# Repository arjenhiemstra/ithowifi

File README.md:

# ithowifi
ESP based WiFi controller for Itho devices

*(note: I'm in no way a professional hardware/software engineer and have no background in these subjects. I like this for a hobby, to learn and to share my projects)*

Finished boards can be ordered in my webshop:
[https://www.nrgwatch.nl](http://www.nrgwatch.nl)
or in my Tindie store:
[https://www.tindie.com/products/19680/](https://www.tindie.com/products/19680/)

|CVE Add-on|non-CVE wifi module|
|:---:|:---:|
|  |  |

## WiFi add-on to control itho central ventilation units

-   Control your Itho Daalderop ventilation unit with one simple add-on module
-   No hardware changes needed to the Itho unit, no warranty void
-   Control fan speed through the web interface, REST API v2, MQTT, or Home Assistant
-   Send remote commands via virtual remotes (I2C) or RF remotes (CC1101 wireless)
-   RF standalone mode for devices without I2C connection (e.g. HRU 400 R)
-   OTA firmware updates directly from the web interface
-   Easily integrate in any home automation system through MQTT or REST API
-   Companion integrations available:
    - [Home Assistant](https://github.com/arjenhiemstra/ithowifi-ha-integration) (REST API, automatic discovery)
    - [Home Assistant](https://github.com/jasperslits/haithowifi) (MQTT API, feature rich)
    - [Homey](https://homey.app/en-nl/app/nl.monkeysoft.nrgwatch/Itho-Daalderop/) (REST API)
-   Installation can be done in minutes
-   Detailed installation manual and setup wizard

### CVE models (IthiWiFi CVE add-on - I2C):
-   CVE ECO 2 (also sold by 'Heatrae Sadia' in the UK)
-   CVE ECO RFT (SE/SP, HE/HP)
-   CVE-S ECO / PAK / Optima / CO2
-   HRU ECO 150E / 150P
-   HRU ECO 200E / 200P (also sold as 'Elektrodesign EHR 140 Akor BP' and 'Heatrae Sadia Advance Plus')

### NON-CVE models (IthiWiFi NON-CVE add-on - I2C):
-   HRU ECO 350 LR / LP / HR / HP
-   HRU ECO LE / HE / LP / HP BAL
-   HRU 3 (3) and HRU 3 (2)
-   HRU ECO 250R / 250P, HRU ECO 300R / 300P and HRU ECO 300 DUO Zone (with adapter board, PCI-e splitter cable and CC1101)
-   DemandFlow / QualityFlow
-   WPU 4G / 5G (heat pump)
-   AutoTemp

### RF standalone mode (IthiWiFi NON-CVE add-on wuth CC1101):
-   HRU 300V, HRU 375V and HRU 400 R
-   Most Itho devices controllable via RF (CC1101 module required)
-   Status data received wirelessly via 31DA/31D9 RF messages
-   Older Itho units that only know the RF protocol from before RAMSES (tested on a CVE ECO 2): send only, with a remote of type "RF (old protocol)"

### HRU models by article number:
Check the article number on the nameplate/sticker of your Itho. x is any digit. A letter after the number (A, S) does not count.

| Model | Article number | Add-on |
|---|---|---|
| HRU ECO 150E / 150P | 03-0001x | CVE add-on |
| HRU ECO 200E / 200P | 03-0040x | CVE add-on |
| HRU ECO 250R / 250P | 03-0021x | non-CVE set (with adapter and RF module) |
| HRU ECO 300R / 300P | 03-0030x, 03-00500, 03-00501 | non-CVE set (with adapter and RF module) |
| HRU ECO 300 DUO Zone | 03-00502 | non-CVE set (with adapter and RF module) |
| HRU ECO 350 LR / LP / HR / HP | 03-00389, 03-0039x | non-CVE add-on |
| HRU 300V | 03-00851 | non-CVE add-on + RF module |
| HRU 375V | 03-00853 | non-CVE add-on + RF module |
| HRU 400 R | 03-00584 | non-CVE add-on + RF module |
| HRU ECO LE / HE / LP / HP BAL | 545-426x, 545-427x | non-CVE add-on |
| HRU 3 (3) | 545-421x to 545-425x | non-CVE add-on |
| HRU 3 (2) | 545-41xx, 542-0005 | non-CVE add-on |
| HRU 3 (1) | 545-40xx | Not supported |
| HRU 2 | 540-7003 to 540-7009, 540-7010, 540-702x | Not supported |
| HRU 1 | 540-7001, 540-7002 | Not supported |

####   Note about CVE and HRU ECO 200 firmware:
The CVE add-on controls the Itho unit in standard or medium mode setting only. If you leave the Itho in low or high setting, it won't accept I2C commands from the add-on (Itho designed behaviour). Adding a CC1101 RF module and/or using the virtual remote function can circumvent this issue. The virtual remote function can also be used to force medium mode before sending commands.

## APIs

The add-on provides multiple ways to integrate with your home automation system:

-   **REST API v2** — RESTful endpoints at `/api/v2/*` with JSON request/response format. [OpenAPI spec](https://github.com/arjenhiemstra/ithowifi/wiki/REST-API-v2) available.
-   **MQTT** — publish device status, receive commands. Compatible with Home Assistant MQTT Discovery.
-   **WebSocket** — real-time bidirectional communication used by the web interface.

## OTA Firmware Updates

Firmware can be updated directly from the web interface:
-   Select a firmware version from the dropdown (stable and beta versions available)
-   Click Install — the device downloads and flashes the firmware automatically
-   Manual upload via file is also supported

## Hardware:

A sample hardware design (KiCad) is included, this module can be plugged on the Itho main PCB directly without extra components.
The design files and BOM can be found in the [hardware repo](https://github.com/arjenhiemstra/ithowifi_hardware).

## Further information:

More information is available on the wiki and in the manual:
|  |  |
|---|---|
|Wiki:  |https://github.com/arjenhiemstra/ithowifi/wiki  |
|Dutch:  |https://github.com/arjenhiemstra/ithowifi/raw/master/handleiding.pdf  |
|English:  |https://github.com/arjenhiemstra/ithowifi/raw/master/manual.pdf  |

## Developing / contributing:

For firmware architecture, build/test commands, and AI-assisted development guidelines, start at [AGENTS.md](AGENTS.md). Architectural decisions are tracked in [docs/adr/](docs/adr/), and new features/changes should have a spec in [specs/](specs/).

## Support this project:
If you like this project and would like to support it, please contribute with code updates, wiki edits, pull requests etc. You could also buy me a coffee as appreciation.
I will be really thankfull for anything even if it is just a kind comment towards my work, because that helps me a lot.

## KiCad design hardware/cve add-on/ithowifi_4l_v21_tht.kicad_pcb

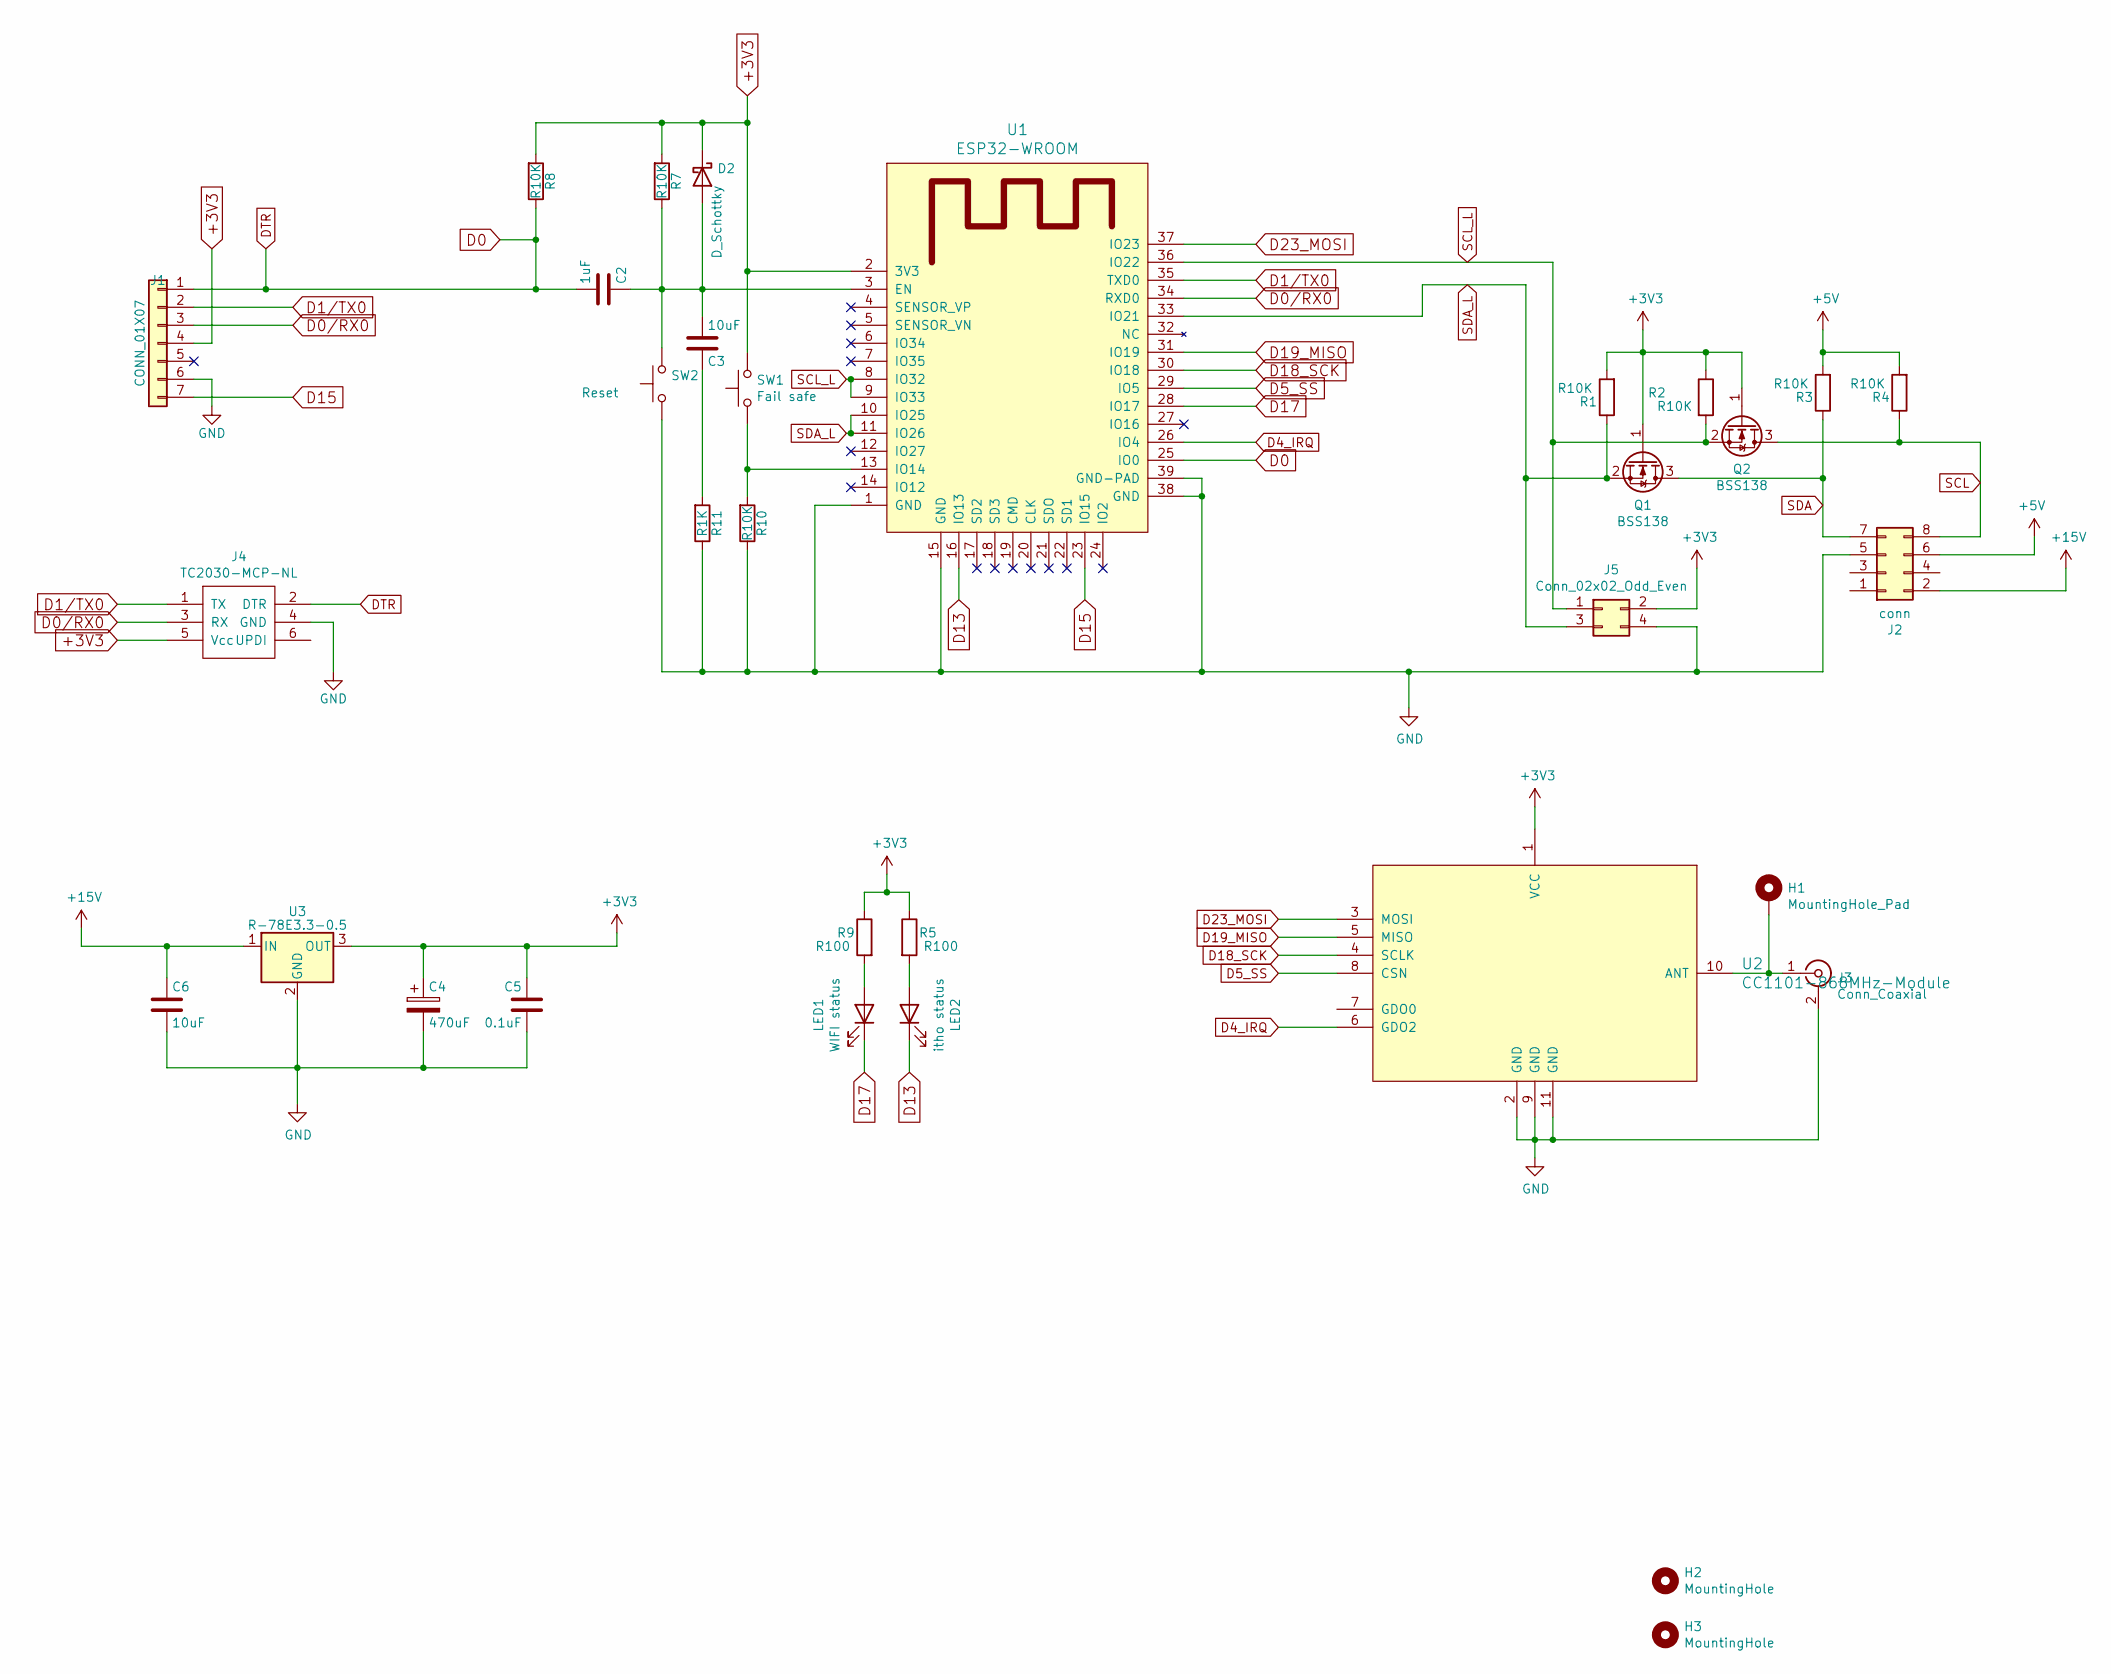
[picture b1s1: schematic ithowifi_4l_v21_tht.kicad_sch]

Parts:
C2: 1uF; C_0805_2012Metric; LCSC C28323
C3: 10uF; C_0805_2012Metric; LCSC C28323
C4: 470uF; CP_EIA-7343-31_Kemet-D; LCSC C7229
C5: 0.1uF; C_0805_2012Metric; LCSC C49678
C6: 10uF; C_0805_2012Metric; LCSC C110053
D2: D_Schottky; D_SOD-123
H1: MountingHole_Pad; Pin_D1.0mm_L10.0mm
H2, H3: MountingHole; MountingHole_2.5mm
J1: CONN_01X07; PinHeader_1x07_P2.54mm_Vertical
J2: conn; PinSocket_2x04_P2.54mm_Vertical
J3: Conn_Coaxial; SMA_Amphenol_132289_EdgeMount
J4: TC2030-MCP-NL; TC2020-MCP-NL
J5: Conn_02x02_Odd_Even; PinHeader_2x02_P2.54mm_Vertical
LED1: WIFI status; LED_0805_2012Metric; LCSC C2293
LED2: itho status; LED_0805_2012Metric; LCSC C2293
Q1, Q2: BSS138; SOT-23W; LCSC C170166
R1, R2, R3, R4, R7, R8, R10: R10K; R_0805_2012Metric; LCSC C17414
R5, R9: R100; R_0805_2012Metric; LCSC C17408
R11: R1K; R_0805_2012Metric; LCSC C17414
SW1: Fail safe; TS-1187; LCSC C92589
SW2: Reset; TS-1187; LCSC C92589
U1: ESP32-WROOM; ESP32-WROOM-32E; LCSC C473012
U2: CC1101-868MHz-Module
U3: R-78E3.3-0.5; Converter_DCDC_RECOM_R-78E-0.5_THT

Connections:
+3V3: C4.1, C5.1, D2.1 (K), J1.4, J4.5 (Vcc), J5.2, Q1.1 (G), Q2.1 (G), R1.2, R2.1, R5.1, R7.2, R8.2, R9.1, SW1.2, U1.2 (3V3), U2.1 (VCC), U3.3 (OUT)
+5V: J2.6, R3.2, R4.2
+15V: C6.1, J2.2, U3.1 (IN)
D0: C2.2, J1.1, J4.2 (DTR), R8.1, U1.25 (IO0)
D0/RX0: J1.3, J4.3 (RX), U1.34 (RXD0)
D1/TX0: J1.2, J4.1 (TX), U1.35 (TXD0)
D4_IRQ: U1.26 (IO4), U2.6 (GDO2)
D5_SS: U1.29 (IO5), U2.8 (CSN)
D13: LED2.1 (K), U1.16 (IO13)
D15: J1.7, U1.23 (IO15)
D17: LED1.1 (K), U1.28 (IO17)
D18_SCK: U1.30 (IO18), U2.4 (SCLK)
D19_MISO: U1.31 (IO19), U2.5 (MISO)
D23_MOSI: U1.37 (IO23), U2.3 (MOSI)
GND: C4.2, C5.2, C6.2, J1.6, J2.5, J3.2 (Ext), J4.4 (GND), J5.4, R10.1, R11.1, SW2.1, U1.1 (GND), U1.15 (GND), U1.38 (GND), U1.39 (GND-PAD), U2.2 (GND), U2.9 (GND), U2.11 (GND), U3.2 (GND)
unnamed: C3.1, R11.2
unnamed: C2.1, C3.2, D2.2 (A), R7.1, SW2.2, U1.3 (EN)
unnamed: H1.1, J3.1 (In), U2.10 (ANT)
unnamed: LED1.2 (A), R9.2
unnamed: LED2.2 (A), R5.2
unnamed: R10.2, SW1.1, U1.13 (IO14)
SCL: J2.8, Q2.3 (D), R4.1
SCL_L: J5.1, Q2.2 (S), R2.2, U1.8 (IO32), U1.9 (IO33), U1.36 (IO22)
SDA: J2.7, Q1.3 (D), R3.1
SDA_L: J5.3, Q1.2 (S), R1.1, U1.10 (IO25), U1.11 (IO26), U1.33 (IO21)

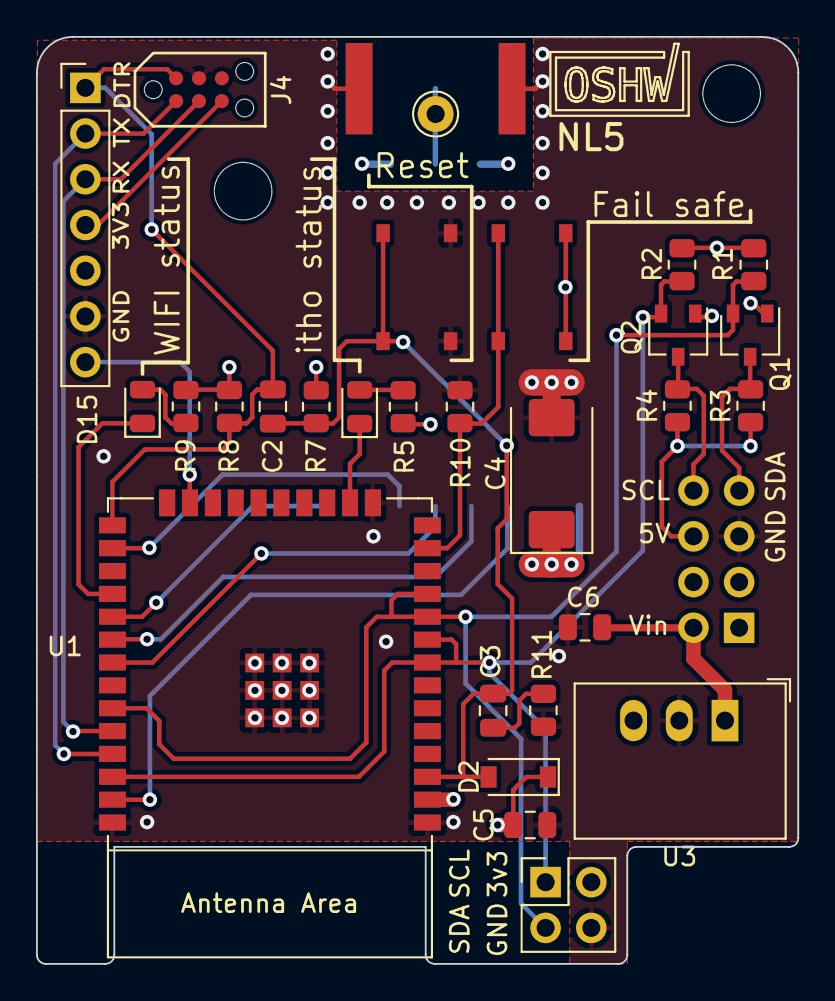
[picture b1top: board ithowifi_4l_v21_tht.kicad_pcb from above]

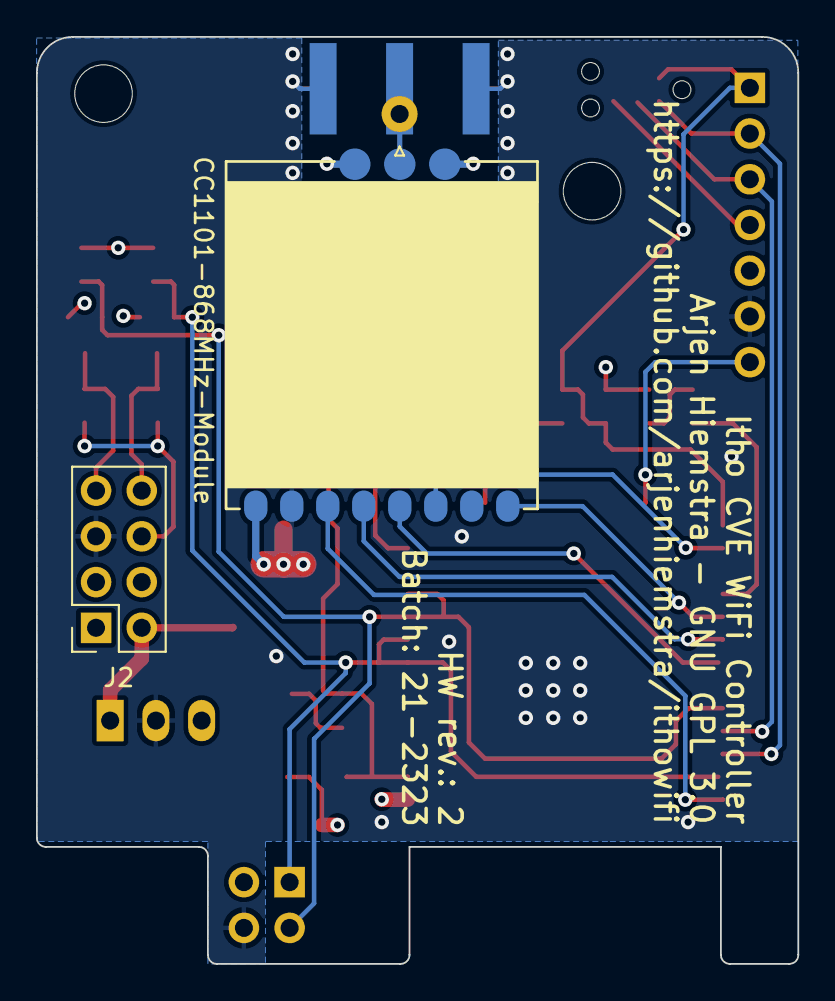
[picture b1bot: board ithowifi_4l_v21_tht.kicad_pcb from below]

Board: 4 copper layers, 42.3 x 51.5 mm, 33 parts (3 on the bottom side), 25 nets.

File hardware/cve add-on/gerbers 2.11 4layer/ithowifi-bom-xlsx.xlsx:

Comment | Designator | Footprint | LCSC Part Number
LED Blue | LED1,LED2 | LED_0805 | C2293
R100 | R9,R5 | 0805 | C17408
10uF | C3, C6 | 0805 | C15850
470uF | C4 | C_Elec_6.3x7.7 | C134738
ESP32-WROOM-32D | U1 | SMD-38_EP_18.0x25.5x1.27P | C82899
B5819W | D1, D2 | SOD-123 | C8598
0,1uF | C5 | 0805 | C49678
1uF | C2 | 0805 | C28323
R10K | R10,R8,R7,R4,R3,R2,R1 | 0805 | C17414
BSS138 | Q2,Q1 | SOT-23-3 | C426569
SW_SPST | SW1,SW2 | SMD-SW-4_5.1X5.1X1.5 | C318884
R1K | R11 | 0805 | C17513

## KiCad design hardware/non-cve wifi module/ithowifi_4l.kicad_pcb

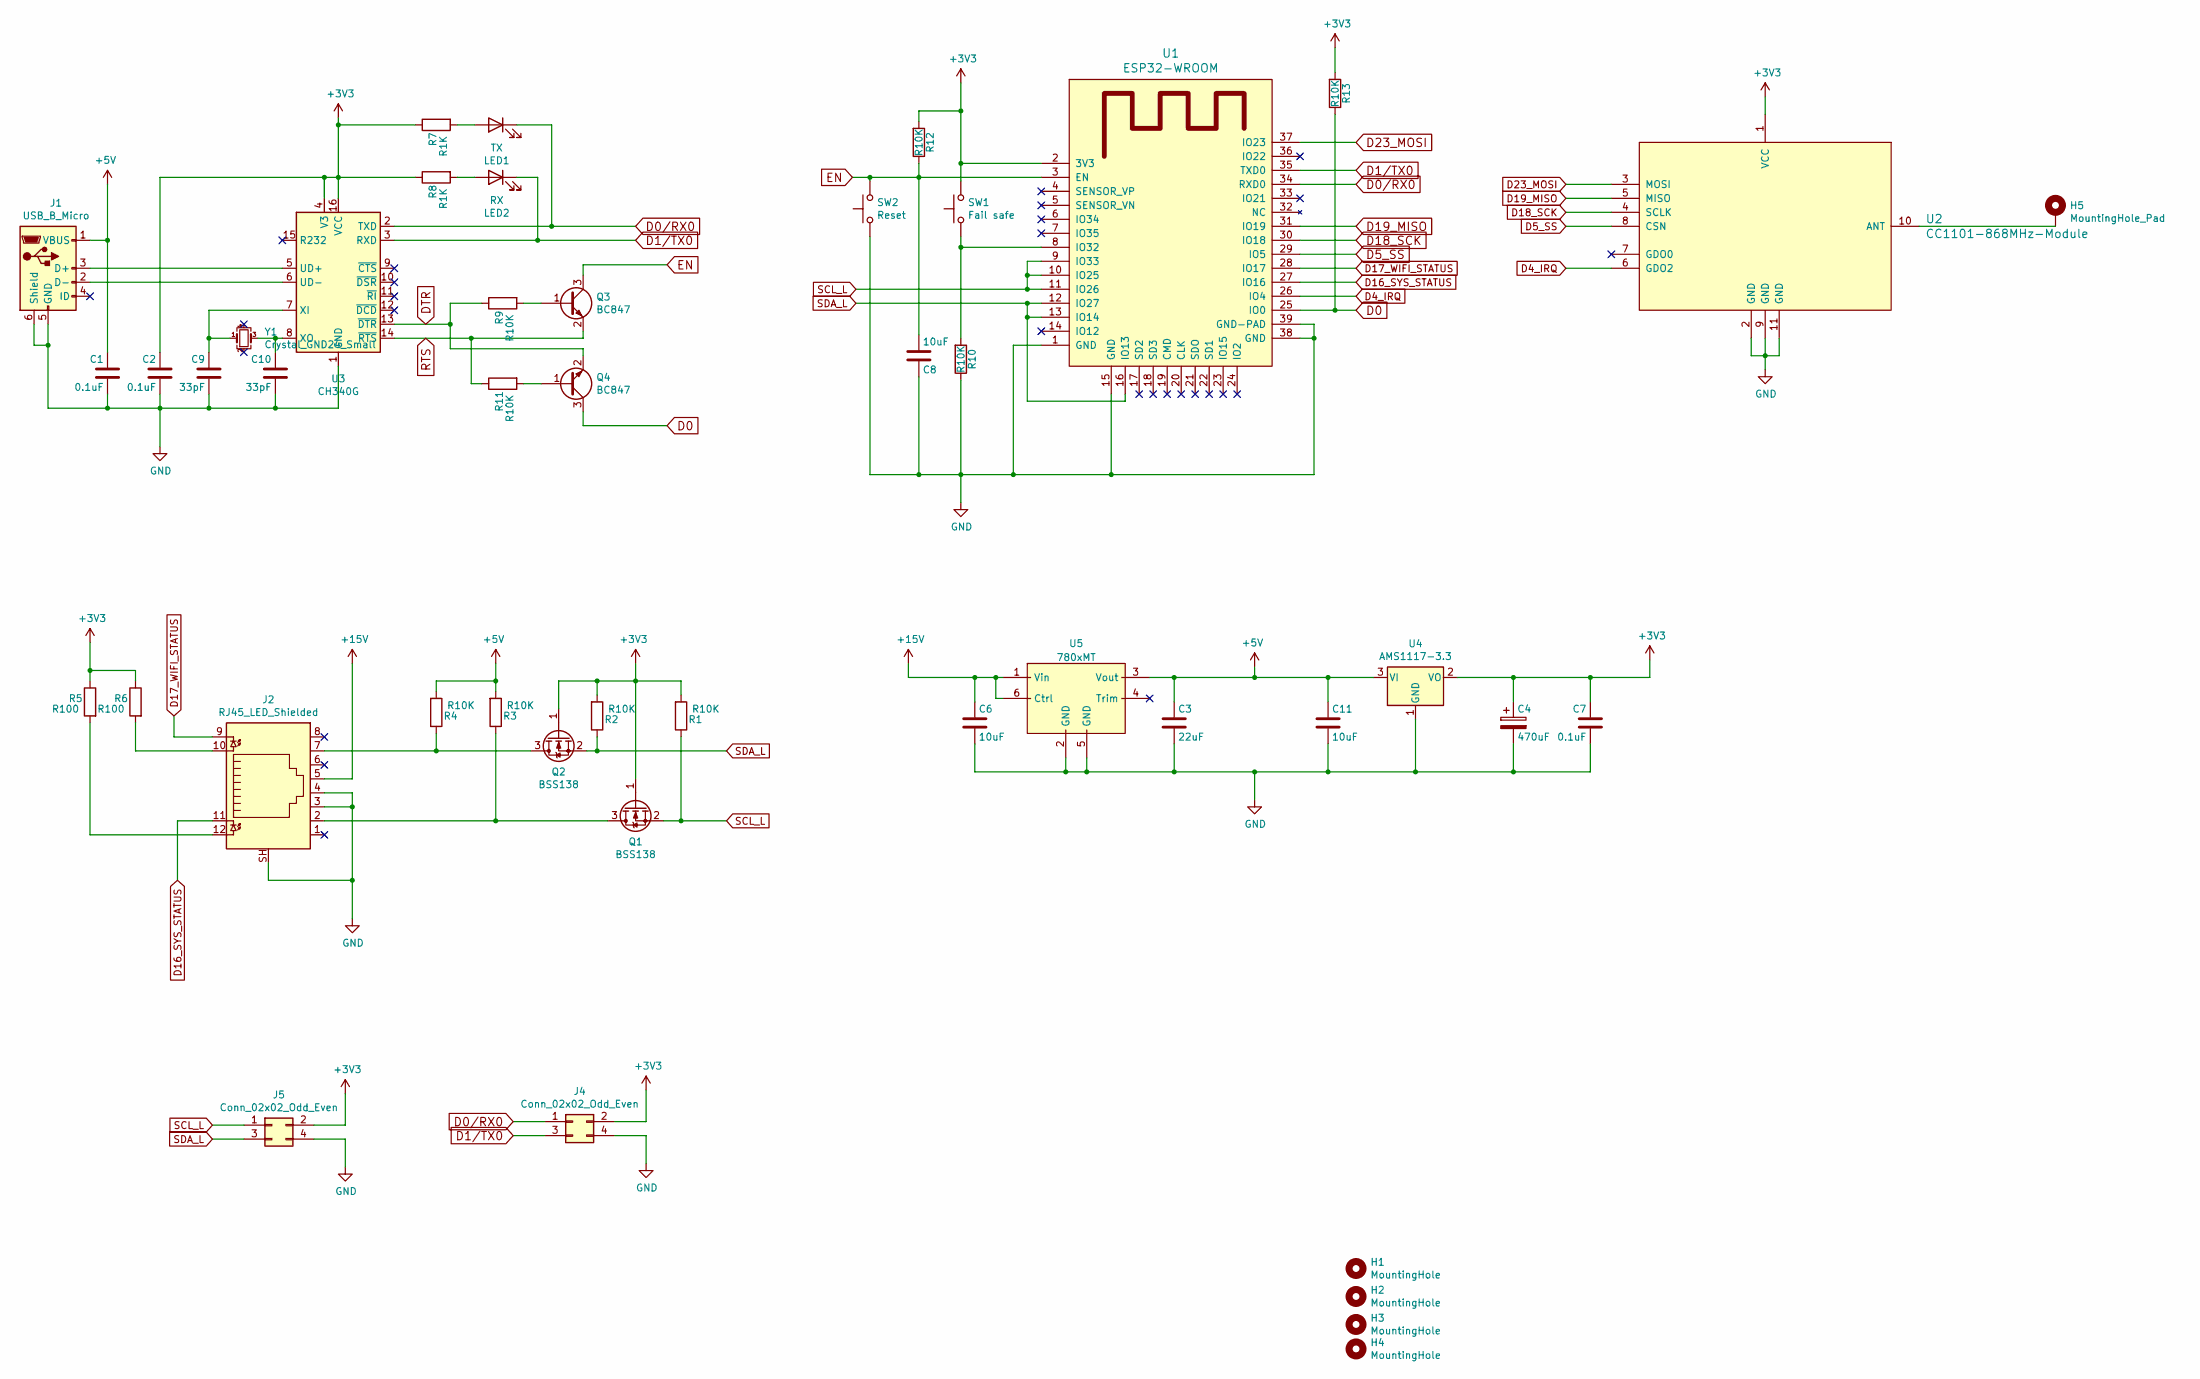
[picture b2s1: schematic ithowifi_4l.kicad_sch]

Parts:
C1, C2, C7: 0.1uF; C_0805_2012Metric
C3: 22uF; C_0805_2012Metric; LCSC C15850
C4: 470uF; CP_EIA-7343-31_Kemet-D; LCSC C7229
C6, C8, C11: 10uF; C_0805_2012Metric; LCSC C15850
C9, C10: 33pF; C_0805_2012Metric
H1, H2, H3, H4: MountingHole; MountingHole_2.5mm
H5: MountingHole_Pad; Pin_D1.0mm_L10.0mm
J1: USB_B_Micro; micro usb; LCSC C879723
J2: RJ45_LED_Shielded; RRJ45R08PC000; LCSC C386757
J4, J5: Conn_02x02_Odd_Even; PinHeader_2x02_P2.54mm_Vertical
LED1: TX; LED_0805_2012Metric; LCSC C2293
LED2: RX; LED_0805_2012Metric; LCSC C2293
Q1, Q2: BSS138; SOT-23W; LCSC C170166
Q3, Q4: BC847; SOT-23W; LCSC C6749
R1, R2, R3, R4, R9, R10, R11, R12, R13: R10K; R_0805_2012Metric; LCSC C17414
R5, R6: R100; R_0805_2012Metric; LCSC C17408
R7, R8: R1K; R_0805_2012Metric; LCSC C17513
SW1: Fail safe; TS-1187; LCSC C92589
SW2: Reset; TS-1187; LCSC C92589
U1: ESP32-WROOM; ESP32-WROOM-32E; LCSC C473012
U2: CC1101-868MHz-Module
U3: CH340G; SOIC-16_3.9x9.9mm_P1.27mm
U4: AMS1117-3.3; SOT-223-3_TabPin2
U5: 780xMT; Mornsun 780xMT; LCSC C2684892
Y1: Crystal_GND24_Small; Crystal_SMD_TXC_7M-4Pin_3.2x2.5mm

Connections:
+3V3: C2.1, C4.1, C7.1, J4.2, J5.2, Q1.1 (G), Q2.1 (G), R1.2, R2.2, R5.1, R6.1, R7.1, R8.1, R12.2, R13.2, SW1.2, U1.2 (3V3), U2.1 (VCC), U3.4 (V3), U3.16 (VCC), U4.2 (VO)
+5V: C1.1, C3.1, C11.1, J1.1 (VBUS), R3.2, R4.2, U4.3 (VI), U5.3 (Vout)
+15V: C6.1, J2.5, U5.1 (Vin), U5.6 (Ctrl)
D0: Q4.3 (C), R13.1, U1.25 (IO0)
D0/RX0: J4.1, LED1.1 (K), U1.34 (RXD0), U3.2 (TXD)
D1/TX0: J4.3, LED2.1 (K), U1.35 (TXD0), U3.3 (RXD)
D4_IRQ: U1.26 (IO4), U2.6 (GDO2)
D5_SS: U1.29 (IO5), U2.8 (CSN)
D16_SYS_STATUS: J2.11, U1.27 (IO16)
D17_WIFI_STATUS: J2.9, U1.28 (IO17)
D18_SCK: U1.30 (IO18), U2.4 (SCLK)
D19_MISO: U1.31 (IO19), U2.5 (MISO)
D23_MOSI: U1.37 (IO23), U2.3 (MOSI)
DTR: Q4.2 (E), R9.1, U3.13 (~DTR)
EN: C8.2, Q3.3 (C), R12.1, SW2.2, U1.3 (EN)
GND: C1.2, C2.2, C3.2, C4.2, C6.2, C7.2, C8.1, C9.2, C10.2, C11.2, J1.5 (GND), J1.6 (Shield), J2.3, J2.4, J2.SH, J4.4, J5.4, R10.1, SW2.1, U1.1 (GND), U1.15 (GND), U1.38 (GND), U1.39 (GND-PAD), U2.2 (GND), U2.9 (GND), U2.11 (GND), U3.1 (GND), U4.1 (GND), U5.2 (GND), U5.5 (GND)
unnamed: C9.1, U3.7 (XI), Y1.1
unnamed: C10.1, U3.8 (XO), Y1.3
unnamed: H5.1, U2.10 (ANT)
unnamed: J1.2 (D-), U3.6 (UD-)
unnamed: J1.3 (D+), U3.5 (UD+)
unnamed: J2.2, Q1.3 (D), R3.1
unnamed: J2.7, Q2.3 (D), R4.1
unnamed: J2.10, R6.2
unnamed: J2.12, R5.2
unnamed: LED1.2 (A), R7.2
unnamed: LED2.2 (A), R8.2
unnamed: Q3.1 (B), R9.2
unnamed: Q4.1 (B), R11.2
unnamed: R10.2, SW1.1, U1.8 (IO32)
RTS: Q3.2 (E), R11.1, U3.14 (~RTS)
SCL_L: J5.1, Q1.2 (S), R1.1, U1.9 (IO33), U1.10 (IO25), U1.11 (IO26)
SDA_L: J5.3, Q2.2 (S), R2.1, U1.12 (IO27), U1.13 (IO14), U1.16 (IO13)

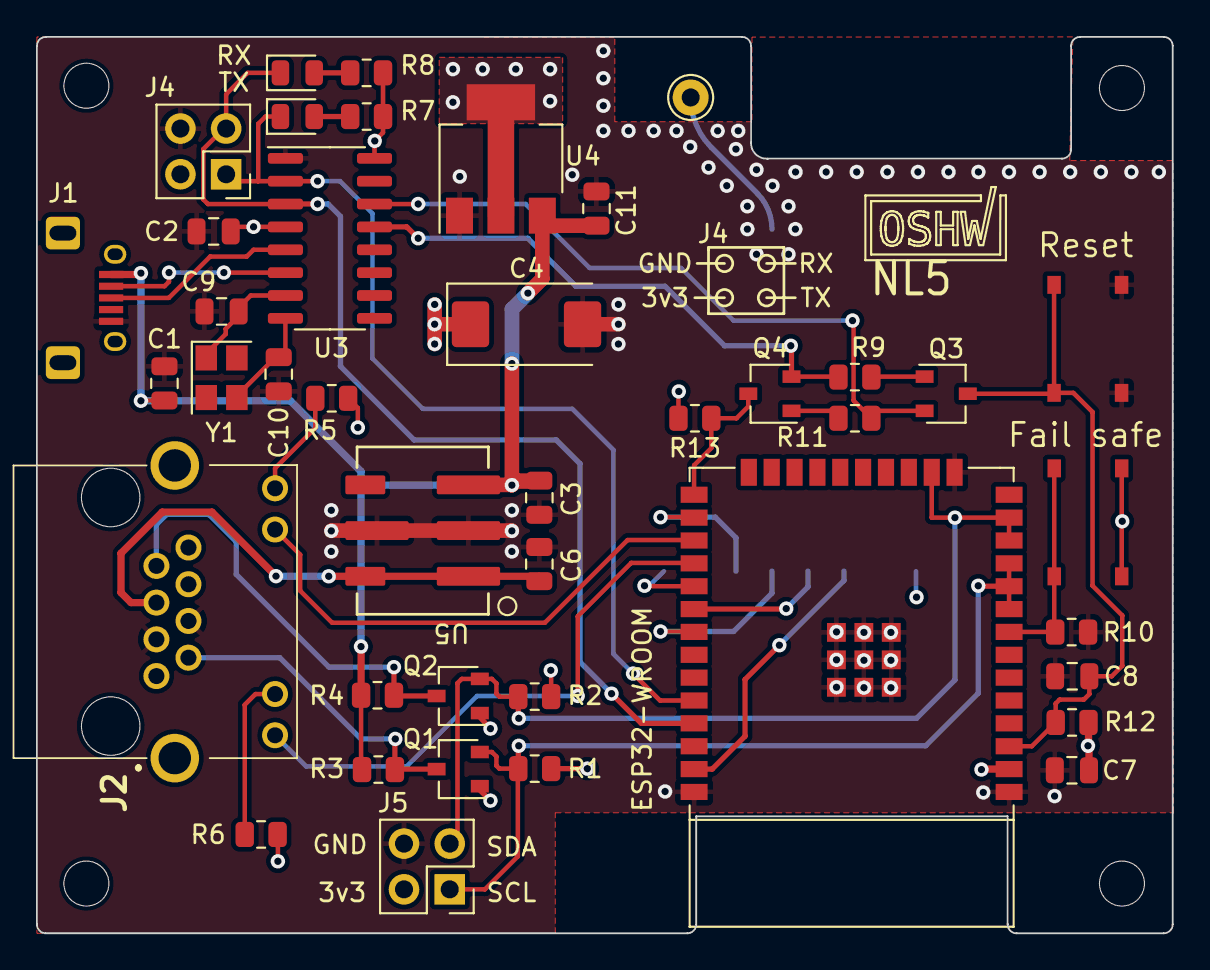
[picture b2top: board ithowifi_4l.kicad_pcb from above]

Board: 4 copper layers, 63.1 x 49.8 mm, 46 parts (1 on the bottom side), 33 nets.

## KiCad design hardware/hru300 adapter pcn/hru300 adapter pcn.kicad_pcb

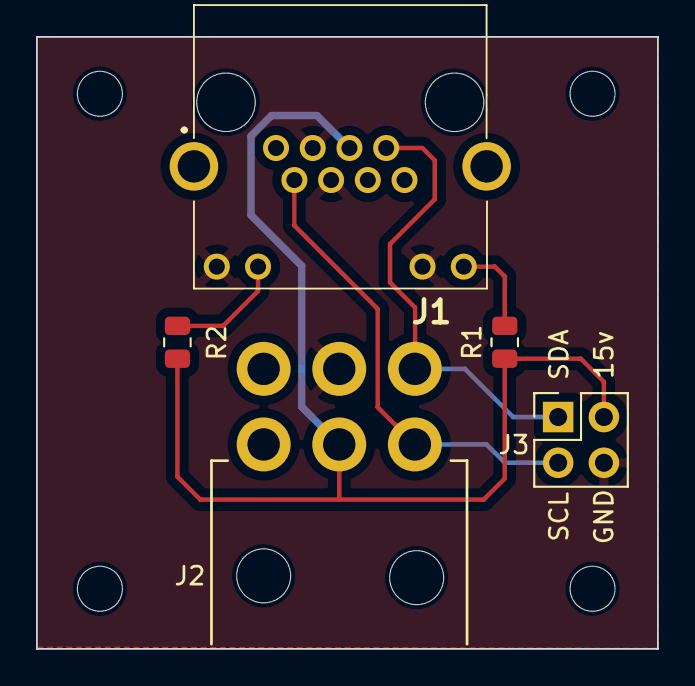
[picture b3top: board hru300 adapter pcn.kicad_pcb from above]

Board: 2 copper layers, 34.5 x 34.0 mm, 9 parts (0 on the bottom side), 6 nets.

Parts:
H1, H2, H3, H4: MountingHole; MountingHole_2.5mm
J1: RJ45_LED_Shielded; RRJ45R08PC000
J2: MOLEX PCI-e conn
J3: Conn_02x02_Odd_Even; PinHeader_2x02_P2.54mm_Vertical
R1, R2: R680; R_0805_2012Metric

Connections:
+15V: J1.5, J2.2, J3.2, R1.1, R2.1
GND: J1.3, J1.4, J1.9, J1.11, J2.5, J3.4
unnamed: J1.10, R2.2
unnamed: J1.12, R1.2
SCL_L: J1.2, J2.1, J3.3
SDA_L: J1.7, J2.4, J3.1

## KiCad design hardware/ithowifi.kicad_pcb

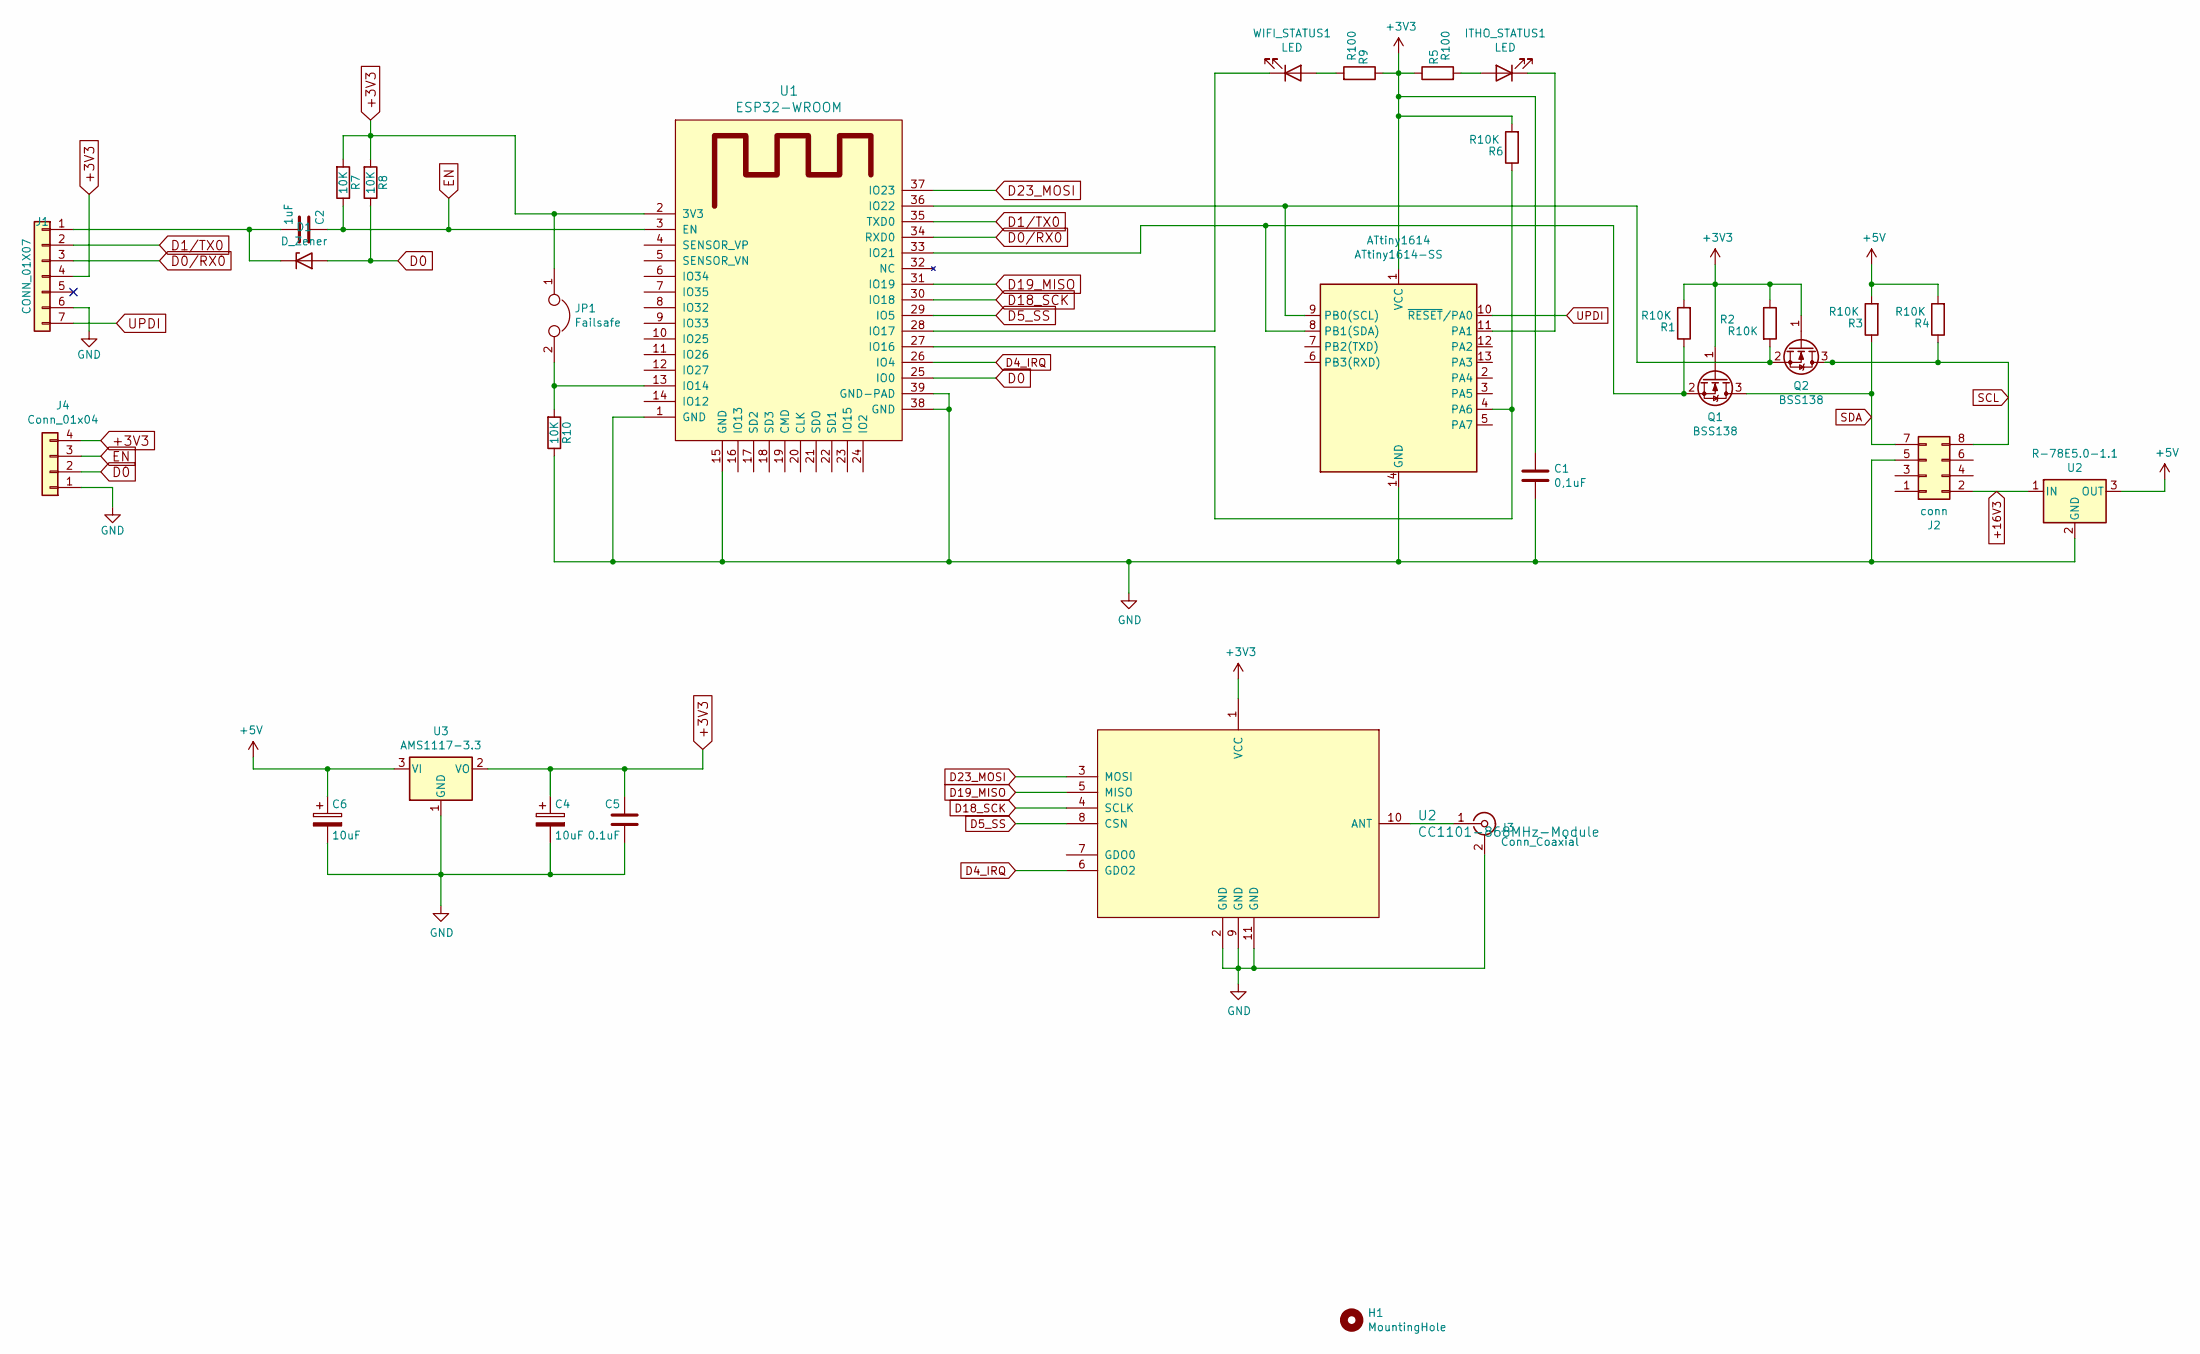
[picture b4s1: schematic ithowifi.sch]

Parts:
ATtiny1614: ATtiny1614-SS; SOIC-14_3.9x8.7mm_P1.27mm
C1: 0,1uF; L_0805_2012Metric
C2: 1uF; C_0805_2012Metric
C4, C6: 10uF; CP_EIA-3216-12_Kemet-S
C5: 0.1uF; C_0805_2012Metric
D1: D_Zener; D_SOD-123
H1: MountingHole; MountingHole_2.5mm
ITHO_STATUS1: LED; LED_0805_2012Metric
J1: CONN_01X07; PinHeader_1x07_P2.54mm_Vertical
J2: conn; PinSocket_2x04_P2.54mm_Vertical
J3: Conn_Coaxial; SMA_Amphenol_132289_EdgeMount
J4: Conn_01x04; PinHeader_1x04_P2.54mm_Vertical
JP1: Failsafe; SolderJumper-2_P1.3mm_Open_RoundedPad1.0x1.5mm
Q1, Q2: BSS138; SOT-23
R1, R2, R3, R4, R6: R10K; R_0805_2012Metric
R5, R9: R100; R_0805_2012Metric
R7, R8, R10: 10K; R_0805_2012Metric
R-78E5.0-1.1: U2; Converter_DCDC_RECOM_R-78E-0.5_THT
U1: ESP32-WROOM; ESP32-WROOM-32
U2: CC1101-868MHz-Module
U3: AMS1117-3.3; SOT-223-3_TabPin2
WIFI_STATUS1: LED; LED_0805_2012Metric

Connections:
+3V3: ATtiny1614.1 (VCC), C1.1, C4.1, C5.1, J1.4, J4.4, JP1.1, Q1.1 (G), Q2.1 (G), R1.2, R2.1, R5.1, R6.2, R7.2, R8.2, R9.1, U1.2 (3V3), U2.1 (VCC), U3.2 (VO)
+5V: C6.1, R3.2, R4.2, R-78E5.0-1.1.3 (OUT), U3.3 (VI)
+16V3: J2.2, R-78E5.0-1.1.1 (IN)
D0: D1.2 (A), J4.2, R8.1, U1.25 (IO0)
D0/RX0: J1.3, U1.34 (RXD0)
D1/TX0: J1.2, U1.35 (TXD0)
D4_IRQ: U1.26 (IO4), U2.6 (GDO2)
D5_SS: U1.29 (IO5), U2.8 (CSN)
D18_SCK: U1.30 (IO18), U2.4 (SCLK)
D19_MISO: U1.31 (IO19), U2.5 (MISO)
D23_MOSI: U1.37 (IO23), U2.3 (MOSI)
EN: C2.1, J4.3, R7.1, U1.3 (EN)
GND: ATtiny1614.14 (GND), C1.2, C4.2, C5.2, C6.2, J1.6, J2.5, J3.2 (Ext), J4.1, R10.1, R-78E5.0-1.1.2 (GND), U1.1 (GND), U1.15 (GND), U1.38 (GND), U1.39 (GND-PAD), U2.2 (GND), U2.9 (GND), U2.11 (GND), U3.1 (GND)
unnamed: ATtiny1614.4 (PA6), R6.1, U1.27 (IO16)
unnamed: ATtiny1614.8 (PB1(SDA)), Q1.2 (S), R1.1, U1.33 (IO21)
unnamed: ATtiny1614.9 (PB0(SCL)), Q2.2 (S), R2.2, U1.36 (IO22)
unnamed: ATtiny1614.11 (PA1), ITHO_STATUS1.1 (K)
unnamed: C2.2, D1.1 (K), J1.1
unnamed: ITHO_STATUS1.2 (A), R5.2
unnamed: J3.1 (In), U2.10 (ANT)
unnamed: JP1.2, R10.2, U1.13 (IO14)
unnamed: R9.2, WIFI_STATUS1.2 (A)
unnamed: U1.28 (IO17), WIFI_STATUS1.1 (K)
SCL: J2.8, Q2.3 (D), R4.1
SDA: J2.7, Q1.3 (D), R3.1
UPDI: ATtiny1614.10 (~RESET~/PA0), J1.7

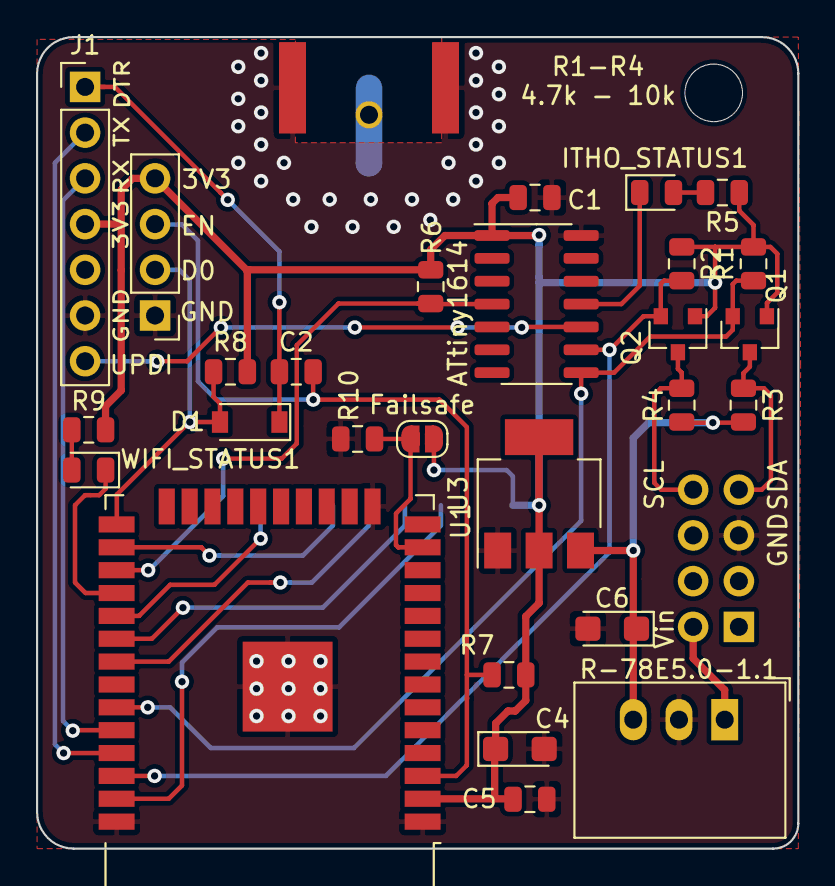
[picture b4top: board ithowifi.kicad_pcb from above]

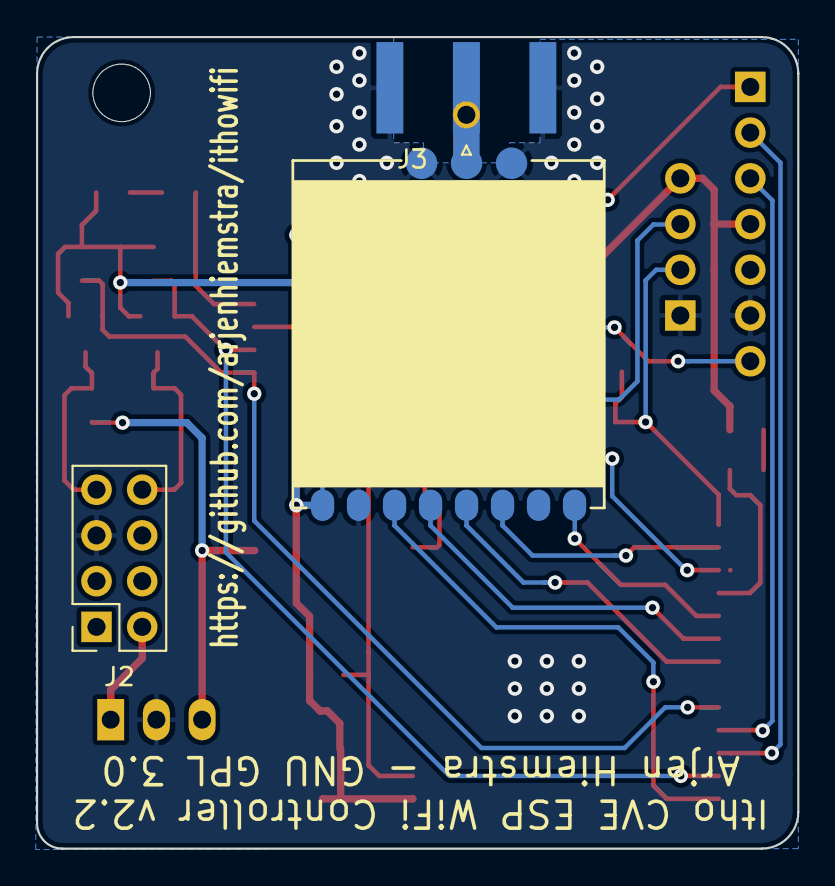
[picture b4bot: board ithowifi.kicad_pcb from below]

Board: 2 copper layers, 42.3 x 45.1 mm, 31 parts (3 on the bottom side), 26 nets.

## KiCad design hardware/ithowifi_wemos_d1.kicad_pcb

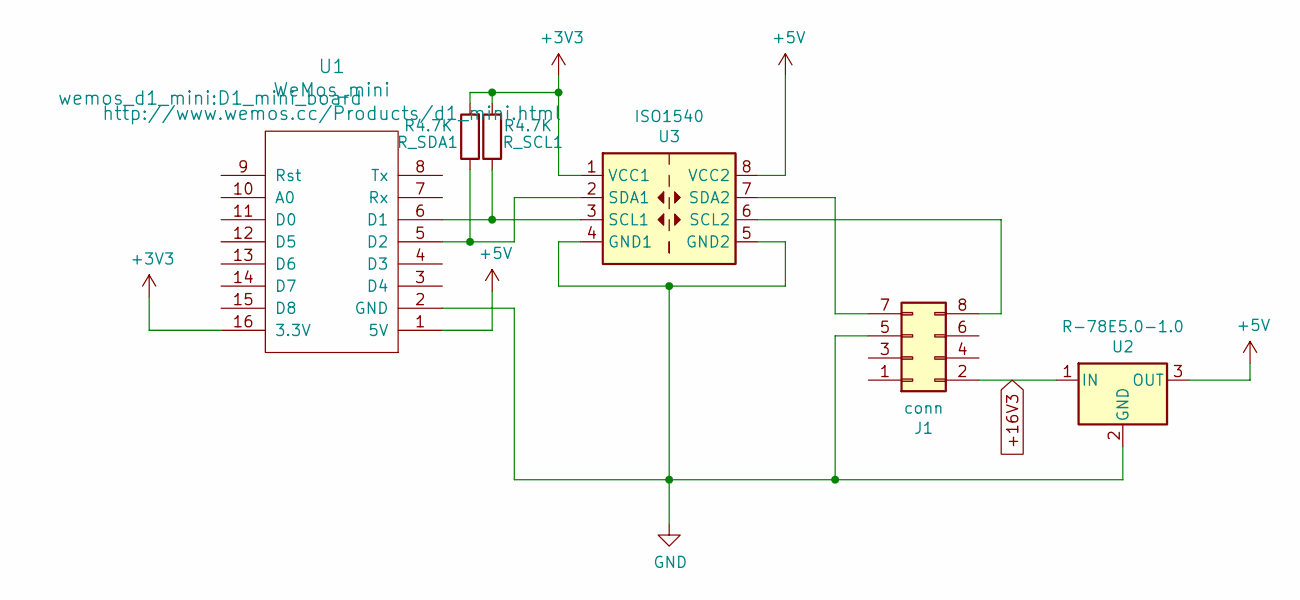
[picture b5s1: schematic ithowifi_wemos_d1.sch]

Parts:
ISO1540: U3; SOIC-8_3.9x4.9mm_P1.27mm
J1: conn; PinSocket_2x04_P2.54mm_Vertical
R-78E5.0-1.0: U2; Converter_DCDC_RECOM_R-78E-0.5_THT
R_SCL1: R4.7K; R_Axial_DIN0309_L9.0mm_D3.2mm_P2.54mm_Vertical
R_SDA1: R4.7K; R_Axial_DIN0309_L9.0mm_D3.2mm_P2.54mm_Vertical
U1: WeMos_mini; D1_mini_board

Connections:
+3V3: ISO1540.1 (VCC1), R_SCL1.2, R_SDA1.2, U1.16 (3.3V)
+5V: ISO1540.8 (VCC2), R-78E5.0-1.0.3 (OUT), U1.1 (5V)
+16V3: J1.2, R-78E5.0-1.0.1 (IN)
GND: ISO1540.4 (GND1), ISO1540.5 (GND2), J1.5, R-78E5.0-1.0.2 (GND), U1.2 (GND)
unnamed: ISO1540.2 (SDA1), R_SDA1.1, U1.5 (D2)
unnamed: ISO1540.3 (SCL1), R_SCL1.1, U1.6 (D1)
unnamed: ISO1540.6 (SCL2), J1.8
unnamed: ISO1540.7 (SDA2), J1.7

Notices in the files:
hardware/cve add-on/ithowifi_4l_v21_tht.kicad_pcb:
Arjen Hiemstra - GNU GPL 3.0
hardware/ithowifi_wemos_d1.kicad_pcb:
GNU General Public License 3.0
